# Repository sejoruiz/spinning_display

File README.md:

spinning_display
================

Spinning Display with AVD chip

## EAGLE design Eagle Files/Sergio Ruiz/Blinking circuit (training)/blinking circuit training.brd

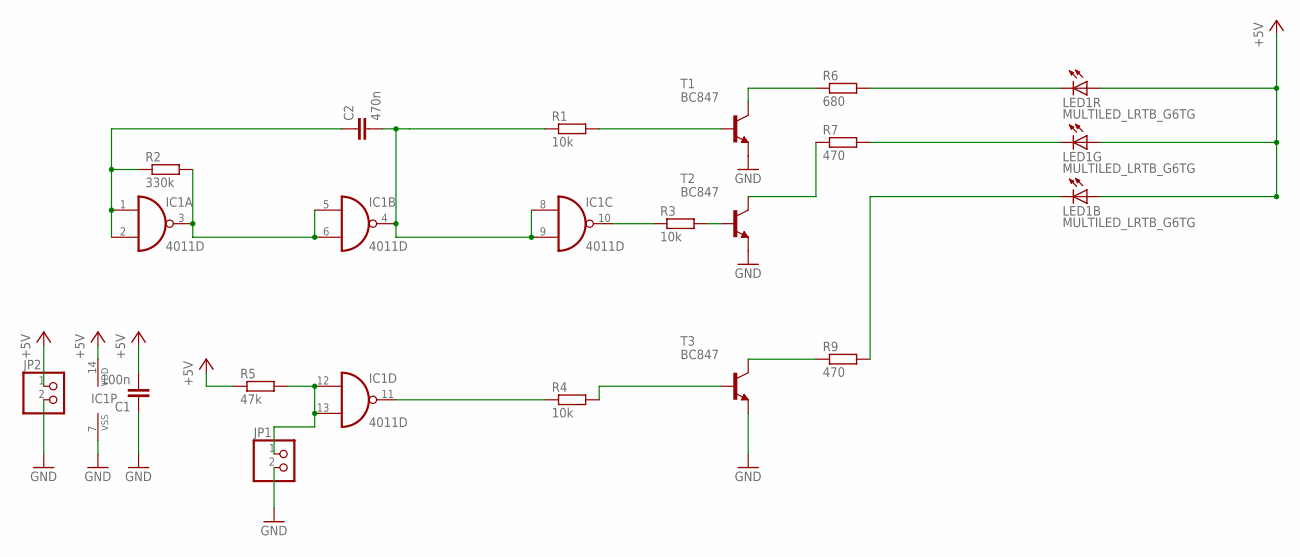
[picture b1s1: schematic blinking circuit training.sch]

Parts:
C1: 100n; C0603
C2: 470n; C0603
IC1: 4011D; SO14
JP1, JP2: PINHD-1X2; 1X02
LED1: MULTILED_LRTB_G6TG; P-LCC-6_TOPLED
R1, R3, R4: 10k; M1206
R2: 330k; M1206
R5: 47k; M1206
R6: 680; M1206
R7, R9: 470; M1206
T1, T2, T3: BC847; SOT23

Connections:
+5V: C1.2, IC1.14 (VDD), JP2.1, LED1.A1 (A), LED1.A2 (A), LED1.A3 (A), R5.1
GND: C1.1, IC1.7 (VSS), JP1.2, JP2.2, T1.2 (E), T2.2 (E), T3.2 (E)
unnamed: C2.1, IC1.1 (I0), IC1.2 (I1), R2.1
unnamed: C2.2, IC1.4 (O), IC1.8 (I0), IC1.9 (I1), R1.1
unnamed: IC1.3 (O), IC1.5 (I0), IC1.6 (I1), R2.2
unnamed: LED1.C1 (C), R6.2
unnamed: R6.1, T1.3 (C)
unnamed: R7.1, T2.3 (C)
unnamed: R3.2, T2.1 (B)
unnamed: IC1.10 (O), R3.1
unnamed: R1.2, T1.1 (B)
unnamed: R9.1, T3.3 (C)
unnamed: IC1.11 (O), R4.1
unnamed: R4.2, T3.1 (B)
unnamed: LED1.C2 (C), R7.2
unnamed: LED1.C3 (C), R9.2
unnamed: IC1.12 (I0), IC1.13 (I1), JP1.1, R5.2

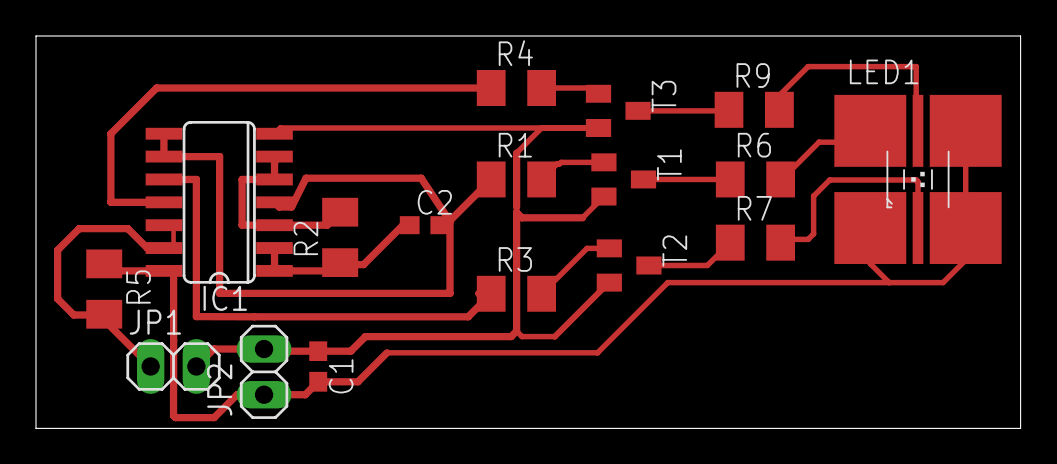
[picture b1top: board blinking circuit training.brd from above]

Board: 2 copper layers, 54.7 x 21.8 mm, 17 parts (0 on the bottom side), 17 nets.

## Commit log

2013-05-10 Project src and Eagle layouts for a spinning display based on AVD microchip
